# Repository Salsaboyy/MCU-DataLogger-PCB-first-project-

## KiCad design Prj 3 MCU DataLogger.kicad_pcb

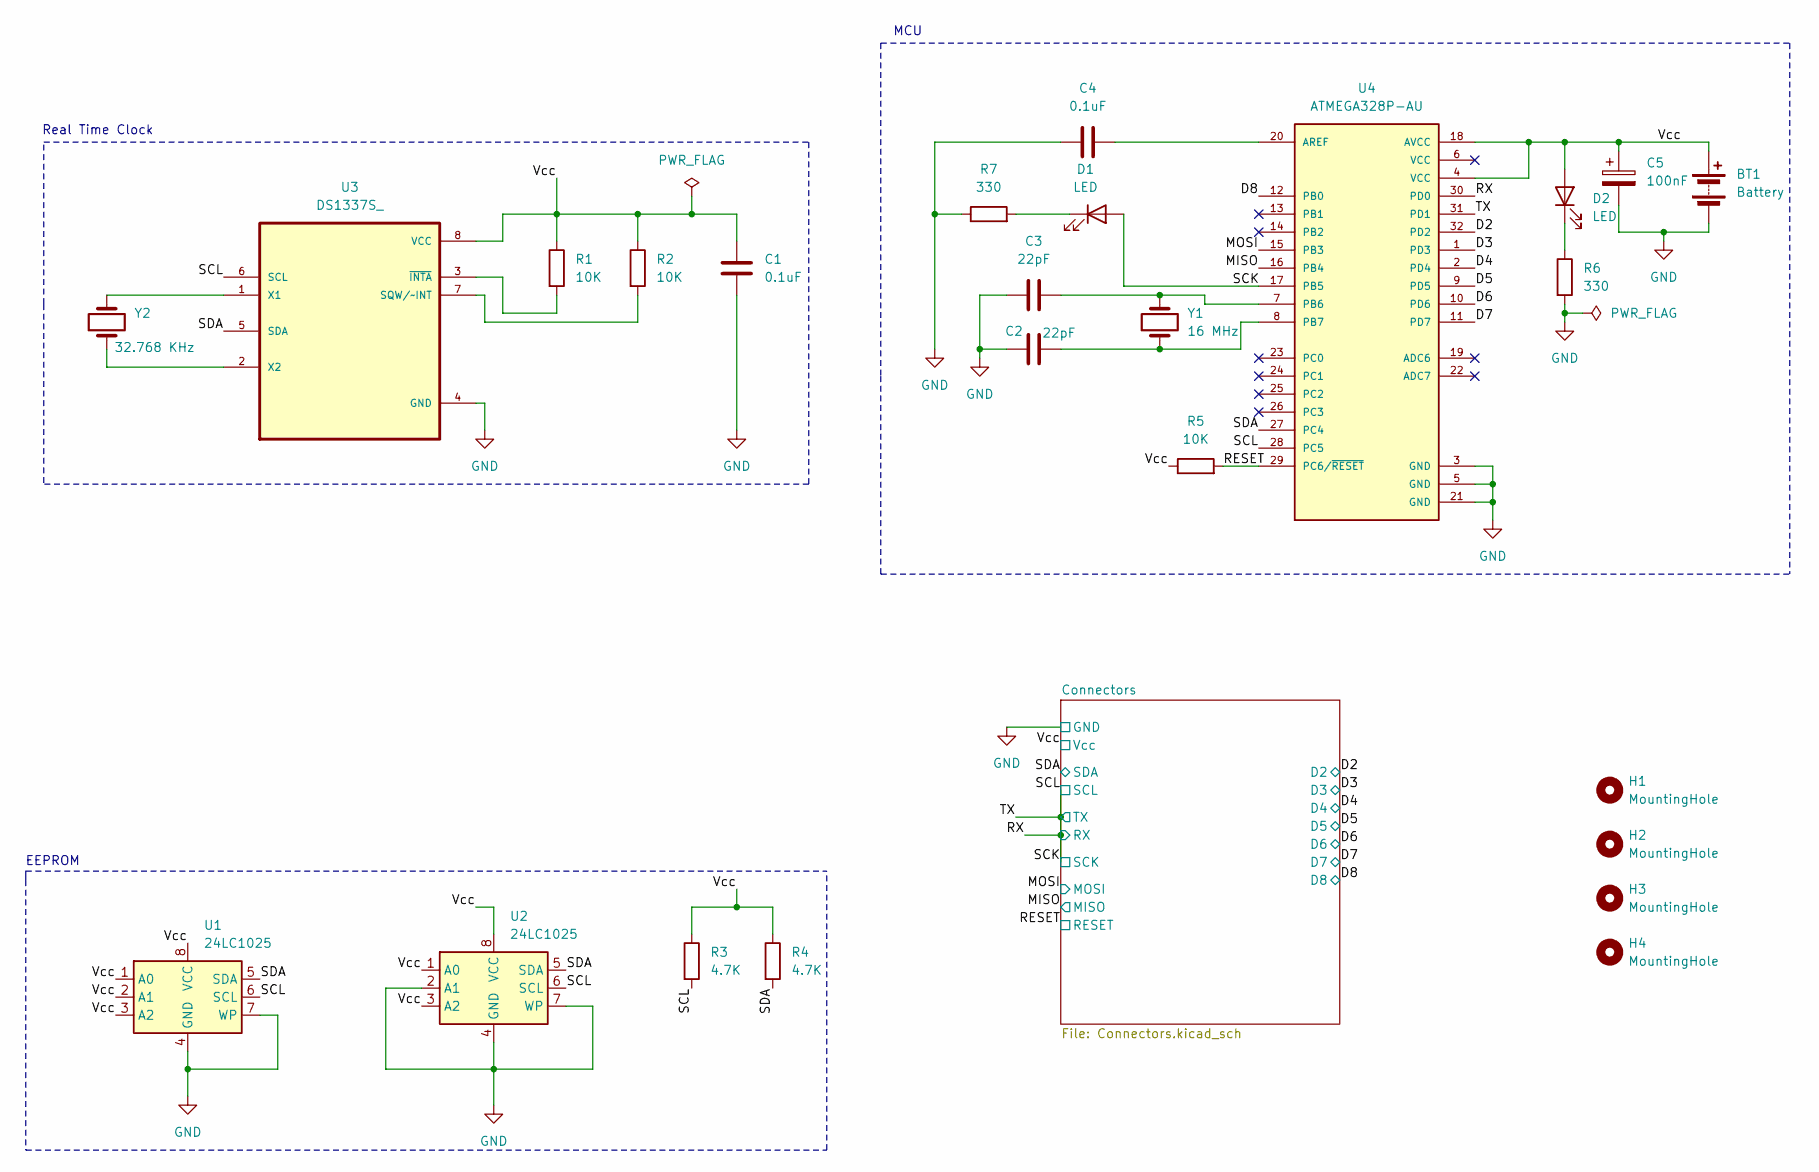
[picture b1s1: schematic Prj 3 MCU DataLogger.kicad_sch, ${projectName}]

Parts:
BT1: Battery; PinHeader_1x02_P2.54mm_Vertical
C1, C4: 0.1uF; C_0805_2012Metric
C2, C3: 22pF; C_0805_2012Metric
C5: 100nF; C_0805_2012Metric
D1, D2: LED; LED_0805_2012Metric
H1, H2, H3, H4: MountingHole; MountingHole_2.1mm
R1, R2, R5: 10K; R_0805_2012Metric
R3, R4: 4.7K; R_0805_2012Metric
R6, R7: 330; R_0805_2012Metric
U1, U2: 24LC1025; SOIC-8_5.23x5.23mm_P1.27mm
U3: DS1337S_; SOIC127P600X175-8N
U4: ATMEGA328P-AU; QFP80P900X900X120-32N; PARTREV 8271A
Y1: 16 MHz; Crystal_SMD_5032-2Pin_5.0x3.2mm_HandSoldering
Y2: 32.768 KHz; Crystal_SMD_5032-2Pin_5.0x3.2mm_HandSoldering

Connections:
/D2: U4.32 (PD2); also elsewhere on the board
/D3: U4.1 (PD3); also elsewhere on the board
/D4: U4.2 (PD4); also elsewhere on the board
/D5: U4.9 (PD5); also elsewhere on the board
/D6: U4.10 (PD6); also elsewhere on the board
/D7: U4.11 (PD7); also elsewhere on the board
/D8: U4.12 (PB0); also elsewhere on the board
/MISO: U4.16 (PB4); also elsewhere on the board
/MOSI: U4.15 (PB3); also elsewhere on the board
/RESET: R5.2, U4.29 (PC6/~RESET); also elsewhere on the board
/SDA: R4.2, U1.5 (SDA), U2.5 (SDA), U3.5 (SDA), U4.27 (PC4); also elsewhere on the board
/Vcc: BT1.1 (+), C1.1, C5.1, D2.2 (A), R1.1, R2.1, R3.1, R4.1, R5.1, U1.1 (A0), U1.2 (A1), U1.3 (A2), U1.8 (VCC), U2.1 (A0), U2.3 (A2), U2.8 (VCC), U3.8 (VCC), U4.4 (VCC), U4.18 (AVCC); also elsewhere on the board
GND: BT1.2 (-), C1.2, C2.1, C3.1, C4.1, C5.2, R6.2, R7.1, U1.4 (GND), U1.7 (WP), U2.2 (A1), U2.4 (GND), U2.7 (WP), U3.4 (GND), U4.3 (GND), U4.5 (GND), U4.21 (GND); also elsewhere on the board
unnamed: D1.1 (K), R7.2
unnamed: D2.1 (K), R6.1
unnamed: R2.2, U3.7 (SQW/~INT)
unnamed: U3.1 (X1), Y2.2
unnamed: U3.2 (X2), Y2.1
unnamed: R1.2, U3.3 (~INTA)
unnamed: C4.2, U4.20 (AREF)
unnamed: C3.2, U4.7 (PB6), Y1.2
unnamed: C2.2, U4.8 (PB7), Y1.1

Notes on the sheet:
Real Time Clock
MCU
EEPROM

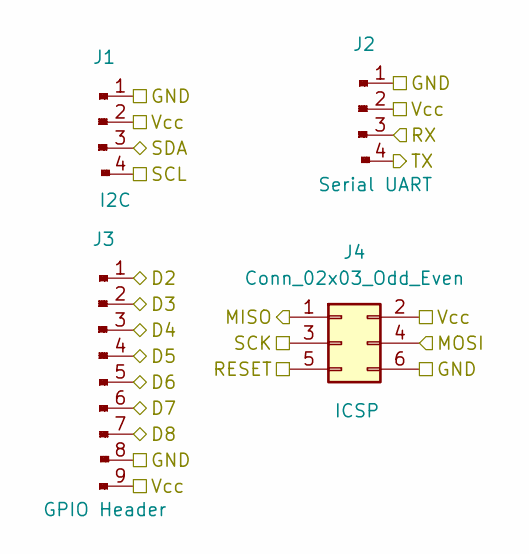
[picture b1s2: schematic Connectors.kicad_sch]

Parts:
J1, J2: Conn_01x04_Male; PinHeader_1x04_P2.54mm_Vertical
J3: Conn_01x09_Male; PinHeader_1x09_P2.54mm_Vertical
J4: Conn_02x03_Odd_Even; PinHeader_2x03_P2.54mm_Vertical

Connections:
/D2: J3.1; also elsewhere on the board
/D3: J3.2; also elsewhere on the board
/D4: J3.3; also elsewhere on the board
/D5: J3.4; also elsewhere on the board
/D6: J3.5; also elsewhere on the board
/D7: J3.6; also elsewhere on the board
/D8: J3.7; also elsewhere on the board
/MISO: J4.1; also elsewhere on the board
/MOSI: J4.4; also elsewhere on the board
/RESET: J4.5; also elsewhere on the board
/SDA: J1.3; also elsewhere on the board
/Vcc: J1.2, J2.2, J3.9, J4.2; also elsewhere on the board
GND: J1.1, J2.1, J3.8, J4.6; also elsewhere on the board

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
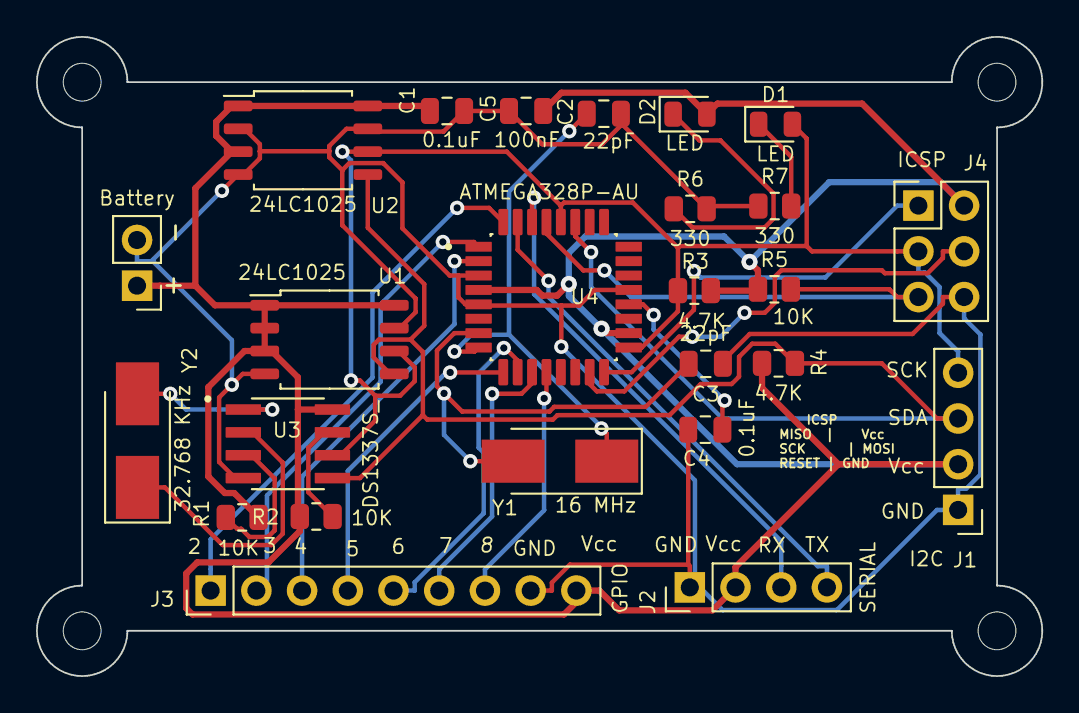
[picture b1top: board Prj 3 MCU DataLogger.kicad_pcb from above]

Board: 2 copper layers, 55.9 x 35.5 mm, 29 parts (0 on the bottom side), 25 nets.

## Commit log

2024-01-01 Setup EEschema for Project.
2024-01-01 Have added all the necessary symbols to my sheets.
2024-01-01 Symbol locations are arranged.
2024-01-01 Symbol locations are arraned & all symbols annotated.
2024-01-01 Component Values are added.
2024-01-01 Symbol to footprint associations are completed.
2024-01-01 Wiring of the root sheet have been completed.
2024-01-01 Wiring of the root sheet is has been completed.
2024-01-01 Second sheets connections are done.
2024-01-01 Second sheets connections are completed.
2024-01-02 Allocated net classes to GND & Vcc to power net class.
2024-01-02 Comments completed.
2024-01-02 Setup Pcbnew.
2024-01-02 Complete footprint placements.
2024-01-02 Routings have been completed except Vcc & GND Copper filled zones.
2024-01-03 Fixed all DRC errors and F&B Silkscreens completed.
2024-01-03 MCU Datalogger with 2 layers Project is completed & Gerbers are imported ; ready for manufacturing.
2024-01-03 MCU Datalogger with 2 layers project is completed & Gerbers are imported , it's ready for manufacturing.
2024-01-03 2 layer PCB is done.
2024-01-03 4layer branch , for 4layer PCB is now created.
2024-01-03 4layer PCB routing is done.
2024-01-03 4 layer PCB for MCU Datalogger Finished.
2024-01-03 Fixed two defects in the schematic.
2024-01-03 4layer PCB is fixed from bugs of the schematics.
2024-01-03 Last commit of 4layer PCB for now.
2024-01-04 Created my image by using image converter with my image.
2024-01-04 Unrouted 4layer PCB.
2024-01-04 Going back usual.
2024-01-04 Switching branches.
2024-01-04 Made a small change.
2024-01-04 2layer PCB is done.
